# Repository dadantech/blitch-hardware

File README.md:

# Agora BLE buttons (blitch)
  
Hardware for Bluetooth buttons with BThome protocol. Works with Home Assistant.

## Firmware
https://github.com/dadantech/blitch-firmware

## 3D models
https://www.thingiverse.com/thing:6855799

## Shop
It is for sale on Tindie: https://www.tindie.com/products/dadantech/agora-ble-buttons/

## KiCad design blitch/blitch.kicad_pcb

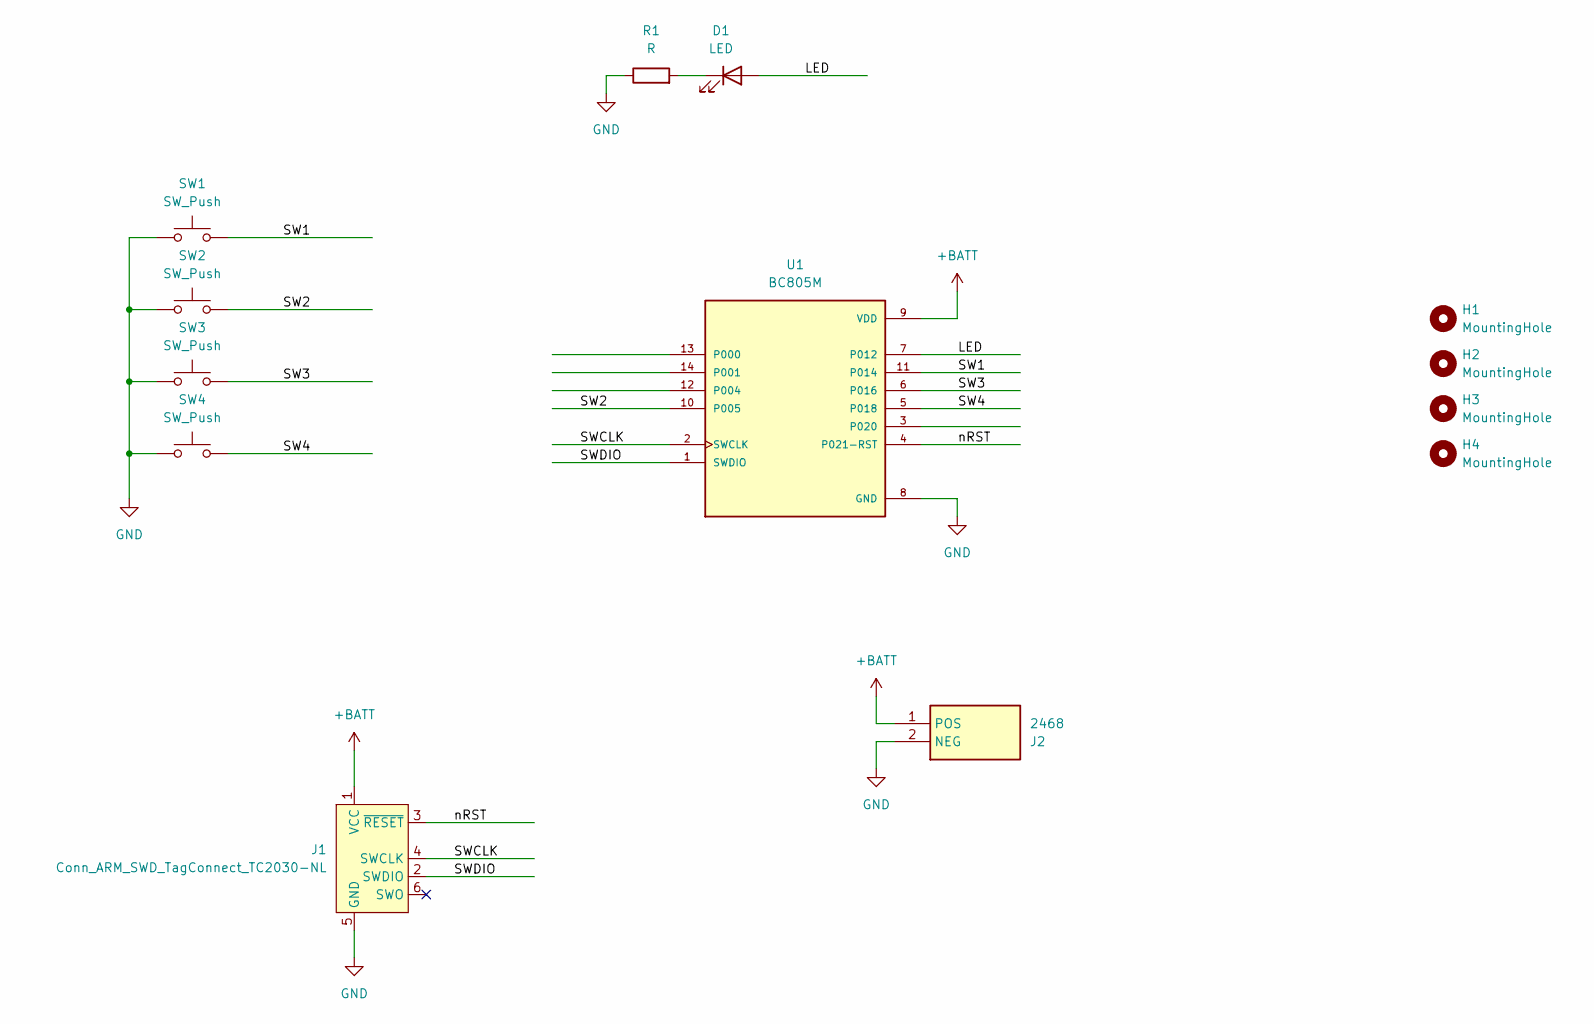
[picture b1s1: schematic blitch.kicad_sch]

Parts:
D1: LED; LED_0603_1608Metric
H1, H2, H3, H4: MountingHole; MountingHole_3.5mm
J1: Conn_ARM_SWD_TagConnect_TC2030-NL; Tag-Connect_TC2030-IDC-NL_2x03_P1.27mm_Vertical
J2: 2468; Mouser Part Number 534-2468
R1: R; R_0603_1608Metric
SW1, SW2, SW3, SW4: SW_Push; SW_SPST_PTS645
U1: BC805M; XCVR_BC805M; PARTREV 1.03

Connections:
+BATT: J1.1 (VCC), J2.1 (POS), U1.9 (VDD)
/LED: D1.2 (A), U1.7 (P012)
/SW1: SW1.2, U1.11 (P014)
/SW2: SW2.2, U1.10 (P005)
/SW3: SW3.2, U1.6 (P016)
/SW4: SW4.2, U1.5 (P018)
/SWCLK: J1.4 (SWCLK), U1.2 (SWCLK)
/SWDIO: J1.2 (SWDIO), U1.1 (SWDIO)
/nRST: J1.3 (~RESET), U1.4 (P021-RST)
GND: J1.5 (GND), J2.2 (NEG), R1.1, SW1.1, SW2.1, SW3.1, SW4.1, U1.8 (GND)
unnamed: D1.1 (K), R1.2

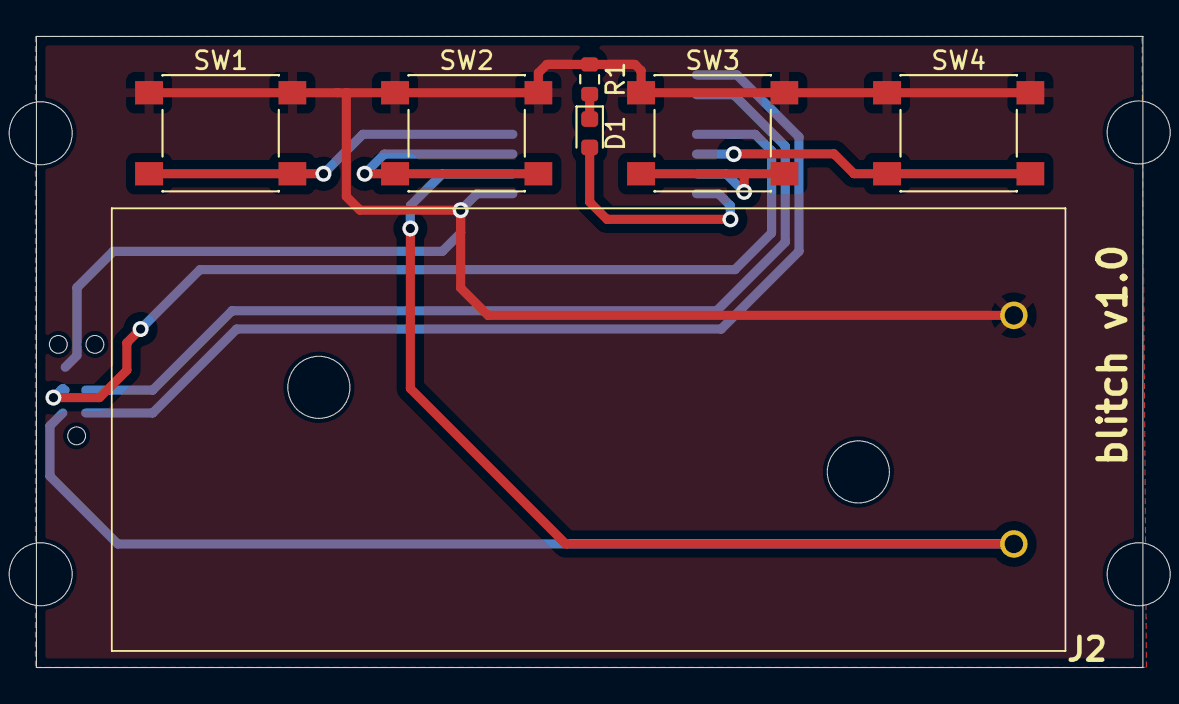
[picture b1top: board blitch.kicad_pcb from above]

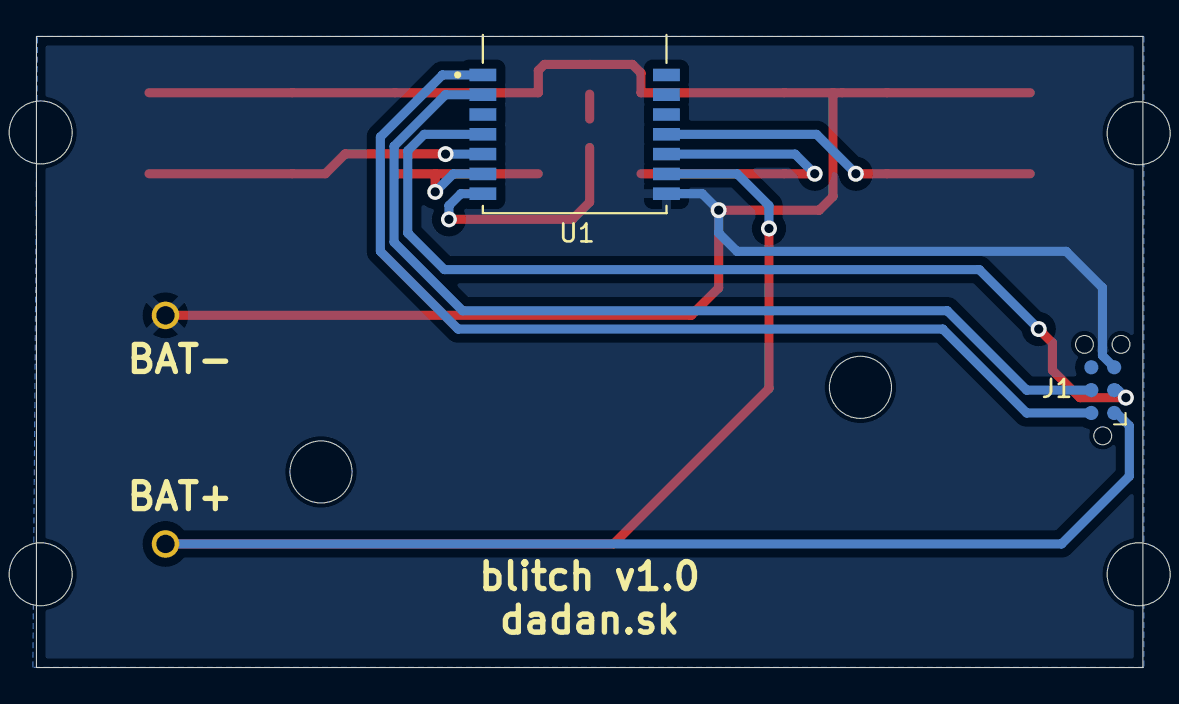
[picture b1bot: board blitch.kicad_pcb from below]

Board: 2 copper layers, 61.5 x 35.1 mm, 13 parts (2 on the bottom side), 11 nets.

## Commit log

2024-10-15 blitch v1.0
2024-10-15 gerber output directory
2024-12-30 Readme
